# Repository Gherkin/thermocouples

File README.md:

# A board for measuring using two thermocouples and a TI ADS1120

ibom: https://gherkin.github.io/thermocouples/

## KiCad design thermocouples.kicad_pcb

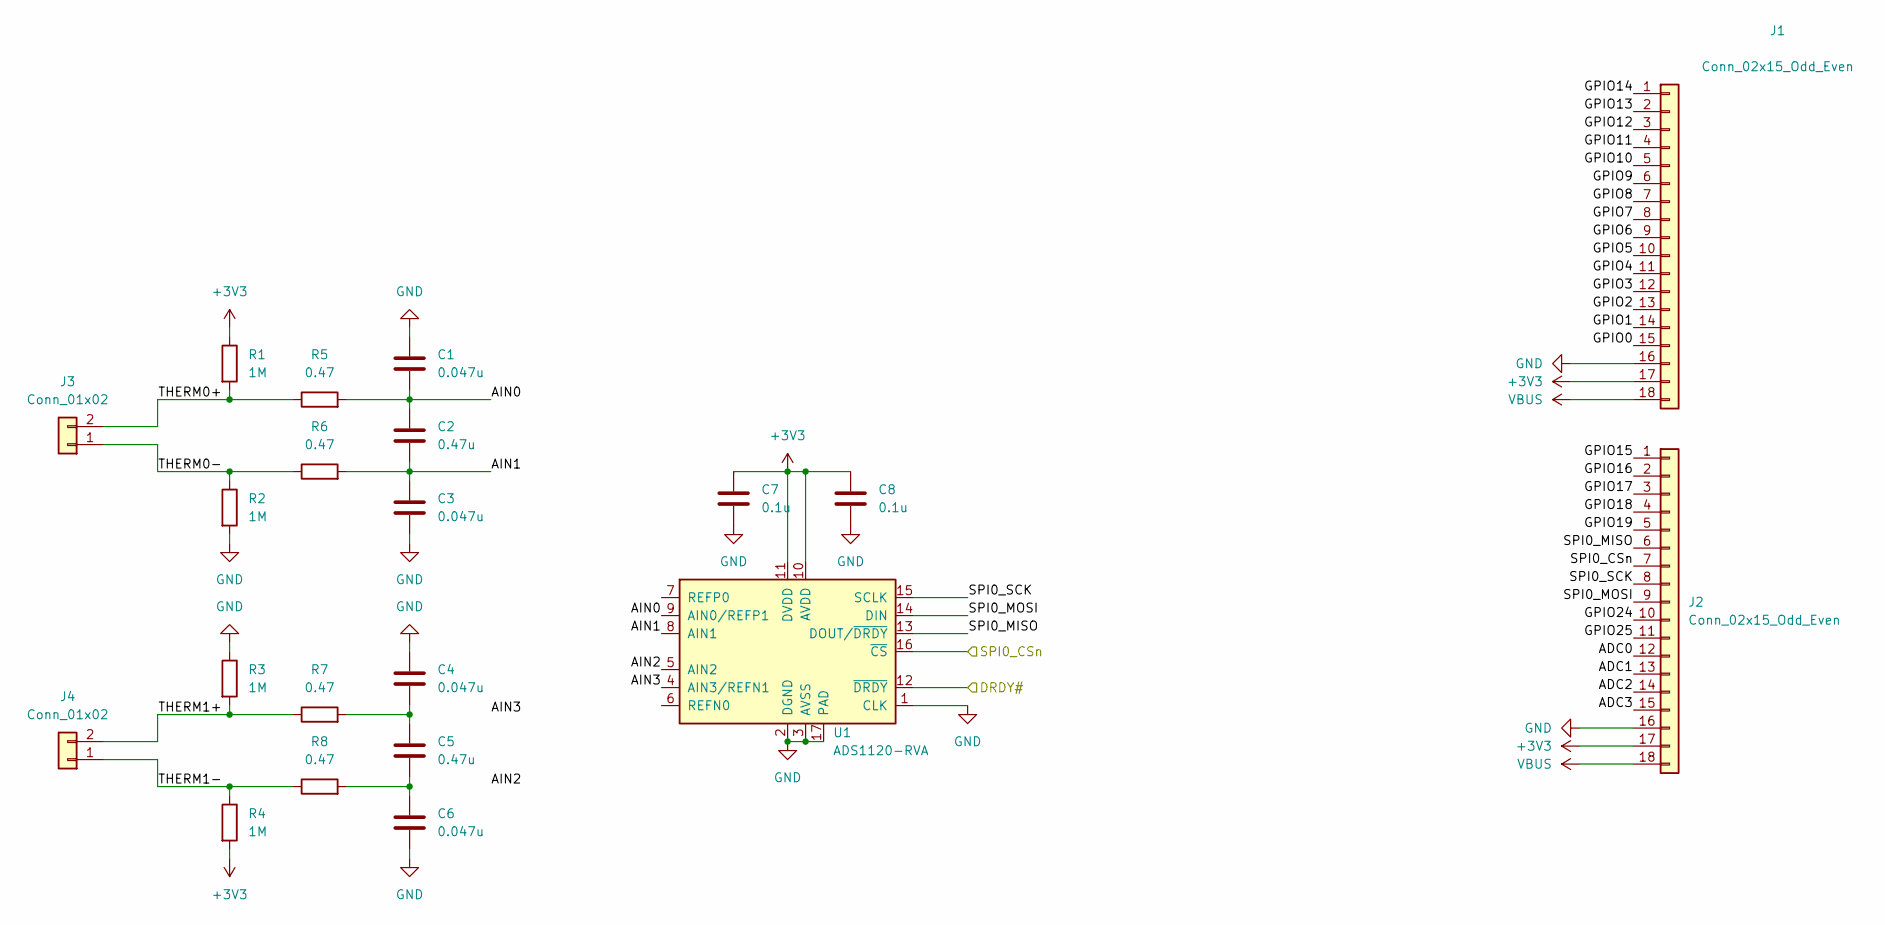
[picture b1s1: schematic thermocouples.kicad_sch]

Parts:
C1, C3, C4, C6: 0.047u; C_0603_1608Metric_Pad1.08x0.95mm_HandSolder; LCSC C1622
C2, C5: 0.47u; C_0603_1608Metric_Pad1.08x0.95mm_HandSolder; LCSC C1623
C7, C8: 0.1u; C_0603_1608Metric_Pad1.08x0.95mm_HandSolder; LCSC C1591
J1, J2: Conn_02x15_Odd_Even; PinSocket_1x18_P2.54mm_Vertical; LCSC C429959
J3, J4: Conn_01x02; TerminalBlock_Phoenix_MKDS-1,5-2_1x02_P5.00mm_Horizontal; LCSC C429959
R1, R2, R3, R4: 1M; R_0603_1608Metric_Pad0.98x0.95mm_HandSolder; LCSC C26098
R5, R6, R7, R8: 0.47; R_0603_1608Metric_Pad0.98x0.95mm_HandSolder; LCSC C23411
U1: ADS1120-RVA; Texas_S-PVQFN-N16_EP2.7x2.7mm; LCSC C2861236

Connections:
+3V3: C7.1, C8.1, J1.17, J2.17, R1.1, R4.2, U1.10 (AVDD), U1.11 (DVDD)
/ADC0: J2.12
/ADC1: J2.13
/ADC2: J2.14
/ADC3: J2.15
/AIN0: C1.2, C2.1, R5.2, U1.9 (AIN0/REFP1)
/AIN1: C2.2, C3.1, R6.2, U1.8 (AIN1)
/AIN2: U1.5 (AIN2)
/AIN3: U1.4 (AIN3/REFN1)
/DRDY#: U1.12 (~DRDY)
/GPIO0: J1.15
/GPIO1: J1.14
/GPIO2: J1.13
/GPIO3: J1.12
/GPIO4: J1.11
/GPIO5: J1.10
/GPIO6: J1.9
/GPIO7: J1.8
/GPIO8: J1.7
/GPIO9: J1.6
/GPIO10: J1.5
/GPIO11: J1.4
/GPIO12: J1.3
/GPIO13: J1.2
/GPIO14: J1.1
/GPIO15: J2.1
/GPIO16: J2.2
/GPIO17: J2.3
/GPIO18: J2.4
/GPIO19: J2.5
/GPIO24: J2.10
/GPIO25: J2.11
/SPI0_CSn: J2.7, U1.16 (~CS)
/SPI0_MISO: J2.6, U1.13 (DOUT/~DRDY)
/SPI0_MOSI: J2.9, U1.14 (DIN)
/SPI0_SCK: J2.8, U1.15 (SCLK)
/THERM0+: J3.2, R1.2, R5.1
/THERM0-: J3.1, R2.1, R6.1
/THERM1+: J4.2, R3.2, R7.1
/THERM1-: J4.1, R4.1, R8.1
GND: C1.1, C3.2, C4.1, C6.2, C7.2, C8.2, J1.16, J2.16, R2.2, R3.1, U1.1 (CLK), U1.2 (DGND), U1.3 (AVSS), U1.17 (PAD)
unnamed: C4.2, C5.1, R7.2
unnamed: C5.2, C6.1, R8.2
VBUS: J1.18, J2.18

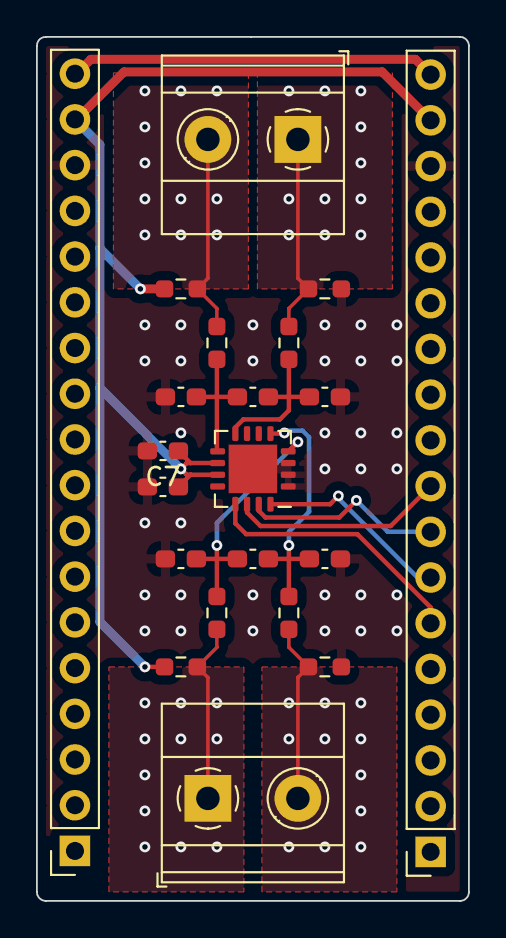
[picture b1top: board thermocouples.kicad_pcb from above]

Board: 2 copper layers, 24.0 x 48.0 mm, 21 parts (0 on the bottom side), 15 nets.

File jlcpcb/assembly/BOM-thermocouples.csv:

Comment,Designator,Footprint,LCSC
0.1u,"C7,C8",C_0603_1608Metric_Pad1.08x0.95mm_HandSolder,C1591
0.047u,"C1,C3,C4,C6",C_0603_1608Metric_Pad1.08x0.95mm_HandSolder,C1622
0.47u,"C2,C5",C_0603_1608Metric_Pad1.08x0.95mm_HandSolder,C1623
0.47,"R5,R6,R7,R8",R_0603_1608Metric_Pad0.98x0.95mm_HandSolder,C23411
1M,"R1,R2,R3,R4",R_0603_1608Metric_Pad0.98x0.95mm_HandSolder,C26098
ADS1120-RVA,U1,Texas_S-PVQFN-N16_EP2.7x2.7mm,C2861236
Conn_02x15_Odd_Even,"J1,J2",PinSocket_1x18_P2.54mm_Vertical,C429959
Conn_01x02,"J3,J4","TerminalBlock_Phoenix_MKDS-1,5-2_1x02_P5.00mm_Horizontal",C8404

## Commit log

2022-06-27 removed backups folder
2022-06-28 sourced all components on lcsc, added ibom and outputs
2022-06-28 added README
2025-03-29 a stencil was lying around
